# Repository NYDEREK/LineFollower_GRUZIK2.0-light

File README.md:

<h1 align="center">GRUZIK2.0: Line Follower Robot</h1>

<div align="center">

<i>Loved the project? Please consider giving a Star ⭐️</i>

</div>

> **GRUZIK2.0 is a lightweight construction (62g) designed for the "Line Follower Light" competition. The robot features Bluetooth communication with a smartphone app and uses a digital sensor instead of analog.**

<div align="center">
  
</div>

<div align="center">

</div>

## Hardware

> **The simple lightweight construction (74g) allows the robot to achieve high speed on the track.**
> **PCBs were designed in KiCAD 7.0 and manufactured by JLCPCB. The rims were 3D printed with PETG for Kyosho "Mini Z" tires.**
> **The light dualsky 150mAh battery provides enough current (max 30C) without adding too much weight (10g).**
> **The Pololu 2211 motor (10:1) with max current 1.6A per one requires the use of two separate TB6612FNG motor drivers with connected channels (max 2A per driver).**
> **The HC-05 Bluetooth module gives communication range up to 10m.**
> **The fast ARM microcontroller STM32F103C8T6 (max 72MHz) provides a lot of software capabilities.**

- uC - STM32F103C8T6
- drivers - TB6612FNG
- sensor - 8x KTIR0711S
- battery - 150mAh LiPo dualsky
- wheels - Kyosho Mini Z
- motors - Pololu 2211
- Bluetooth - HC-05

<div align="center">

</div>

## 📱Bluetooth Apps 📱

> **Thease are simple Bluetooth apps created with MIT App Inventor. Spps start and stop the robot. The Modes pad is responsible for quickly adapting the speed and accuracy of the robot to the route using modes, and the application also displays the battery charge status. Second app is mainly for tweaking PID settings it allows you to change any parameter in seconds**

<div align="center">

</div>

## Credits

> <i>**I implemented the PD controller in my project, drawing inspiration from Bilal Kabas' repository available at - https://github.com/sametoguten/STM32-Line-Follower-with-PID with MIT License - [MIT License](LICENSE)**<i>

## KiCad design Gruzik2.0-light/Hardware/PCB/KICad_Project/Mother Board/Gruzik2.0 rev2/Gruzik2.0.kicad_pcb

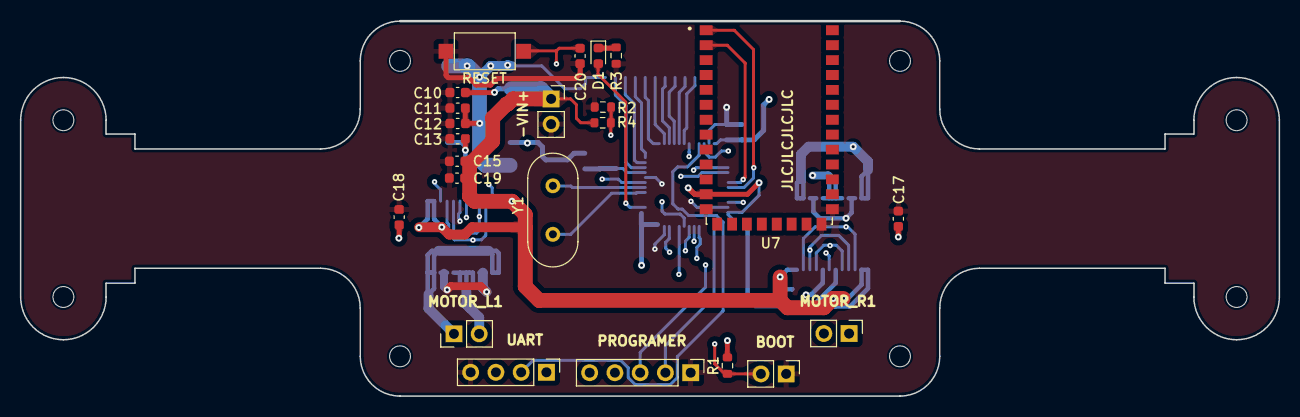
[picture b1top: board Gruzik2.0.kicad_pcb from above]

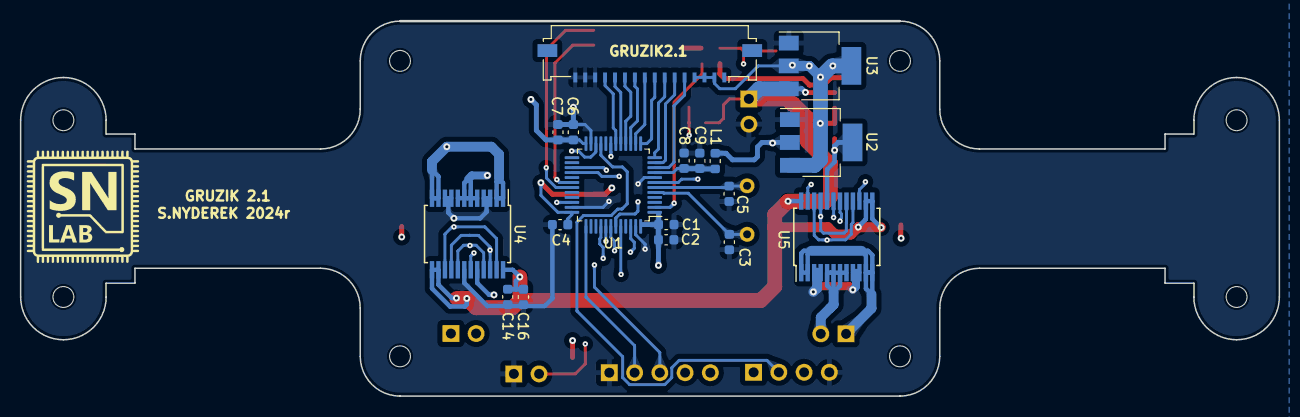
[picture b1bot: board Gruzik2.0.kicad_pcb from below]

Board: 4 copper layers, 126.5 x 37.7 mm, 41 parts (18 on the bottom side), 38 nets.

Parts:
-VIN+: Conn_01x02; PinSocket_1x02_P2.54mm_Vertical
BOOT: Conn_01x02_Pin; PinHeader_1x02_P2.54mm_Vertical
C1: 4u7; C_0603_1608Metric
C2, C4, C6, C7, C9, C20: 100n; C_0603_1608Metric
C3, C5: 20p; C_0603_1608Metric
C8: 1u; C_0603_1608Metric
C10, C12, C16, C19: 10u; C_0603_1608Metric
C11, C13: 33u; C_0603_1608Metric
C14, C15, C17, C18: 0.1u; C_0603_1608Metric
D1: BLUE; LED_0603_1608Metric
GRUZIK2.1: Conn_01x16; Molex_200528-0160_1x16-1MP_P1.00mm_Horizontal
L1: 27n; L_0603_1608Metric
MOTOR_L1: Conn_01x02; PinHeader_1x02_P2.54mm_Vertical
MOTOR_R1: Conn_01x02; PinHeader_1x02_P2.54mm_Vertical
PROGRAMER: Conn_01x05; PinHeader_1x05_P2.54mm_Vertical
R1: 10k; R_0603_1608Metric
R2: 20K; R_0603_1608Metric
R3: 510R; R_0603_1608Metric
R4: 33K; R_0603_1608Metric
RESET: SW_SPST; SW_SPST_CK_RS282G05A3
U1: STM32F103C8T6; LQFP-48_7x7mm_P0.5mm
U2: LM1117MP-3.3; SOT-223-3_TabPin2
U3: LM1117MP-5.0; SOT-223-3_TabPin2
U4, U5: TB6612FNG; SSOP-24_5.3x8.2mm_P0.65mm
U7: HC-05; XCVR_HC-05
UART: Conn_01x04; PinHeader_1x04_P2.54mm_Vertical
Y1: 8MHz; Crystal_HC49-4H_Vertical

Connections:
+3.3V: C1.1, C2.1, C4.1, C6.1, C7.1, C13.1, C17.1, C18.1, L1.1, R1.2, U1.1 (VBAT), U1.24 (VDD), U1.36 (VDD), U1.48 (VDD), U2.2 (VO), U4.20 (VCC), U5.20 (VCC), U7.12 (3.3_VCC)
+3.3VA: C8.1, C9.1, L1.2, U1.9 (VDDA)
+5V: C11.1, C12.1, GRUZIK2.1.2, GRUZIK2.1.3, GRUZIK2.1.4, PROGRAMER.5, U2.3 (VI), U3.2 (VO), UART.1
/BOOT0: BOOT.2, R1.1, U1.44 (BOOT0)
/HSE_IN: C5.1, U1.6 (PD1), Y1.2
/HSE_OUT: C3.1, U1.5 (PD0), Y1.1
GND: -VIN+.2, BOOT.1, C1.2, C2.2, C3.2, C4.2, C5.2, C6.2, C7.2, C8.2, C9.2, C10.2, C11.2, C12.2, C13.2, C14.2, C15.2, C16.2, C17.2, C18.2, C19.2, C20.1, GRUZIK2.1.14, GRUZIK2.1.15, GRUZIK2.1.16, PROGRAMER.1, R2.2, R3.2, RESET.1 (A), U1.8 (VSSA), U1.23 (VSS), U1.35 (VSS), U1.47 (VSS), U2.1 (GND), U3.1 (GND), U4.3 (PGND1), U4.4 (PGND1), U4.9 (PGND2), U4.10 (PGND2), U4.18 (GND), U5.3 (PGND1), U5.4 (PGND1), U5.9 (PGND2), U5.10 (PGND2), U5.18 (GND), U7.13 (GND), U7.21 (GND), U7.22 (GND), UART.4
unnamed: D1.1 (K), R3.1
unnamed: MOTOR_L1.1, U5.1 (AO1), U5.2 (AO1), U5.11 (BO1), U5.12 (BO1)
unnamed: MOTOR_L1.2, U5.5 (AO2), U5.6 (AO2), U5.7 (BO2), U5.8 (BO2)
unnamed: MOTOR_R1.1, U4.1 (AO1), U4.2 (AO1), U4.11 (BO1), U4.12 (BO1)
unnamed: MOTOR_R1.2, U4.5 (AO2), U4.6 (AO2), U4.7 (BO2), U4.8 (BO2)
PA0: GRUZIK2.1.5, U1.10 (PA0)
PA1: GRUZIK2.1.6, U1.11 (PA1)
PA2: GRUZIK2.1.7, U1.12 (PA2)
PA3: GRUZIK2.1.8, U1.13 (PA3)
PA4: GRUZIK2.1.9, U1.14 (PA4)
PA5: GRUZIK2.1.10, U1.15 (PA5)
PA6: GRUZIK2.1.11, U1.16 (PA6)
PA7: GRUZIK2.1.12, U1.17 (PA7)
PA9: U1.30 (PA9), U7.2 (UART-RX)
PA10: U1.31 (PA10), U7.1 (UART-TX)
PB0: GRUZIK2.1.13, U1.18 (PB0)
PB1: R2.1, R4.1, U1.19 (PB1)
PB4: U1.40 (PB4), U4.16 (BIN2), U4.22 (AIN2)
PB5: U1.41 (PB5), U4.17 (BIN1), U4.21 (AIN1)
PB6: U1.42 (PB6), U4.19 (STBY), U5.19 (STBY)
PB7: U1.43 (PB7), U5.15 (PWMB), U5.23 (PWMA)
PB9: U1.46 (PB9), U4.15 (PWMB), U4.23 (PWMA)
PB10: U1.21 (PB10), UART.2
PB11: U1.22 (PB11), UART.3
PB14: U1.27 (PB14), U5.17 (BIN1), U5.21 (AIN1)
PB15: U1.28 (PB15), U5.16 (BIN2), U5.22 (AIN2)
PC13: D1.2 (A), U1.2 (PC13)
RESET: C20.2, PROGRAMER.4, RESET.2 (B), U1.7 (NRST)
SWCLK: PROGRAMER.2, U1.37 (PA14)
SWDIO: PROGRAMER.3, U1.34 (PA13)
VDC: -VIN+.1, C10.1, C14.1, C15.1, C16.1, C19.1, R4.2, U3.3 (VI), U4.13 (VM2), U4.14 (VM3), U4.24 (VM1), U5.13 (VM2), U5.14 (VM3), U5.24 (VM1)

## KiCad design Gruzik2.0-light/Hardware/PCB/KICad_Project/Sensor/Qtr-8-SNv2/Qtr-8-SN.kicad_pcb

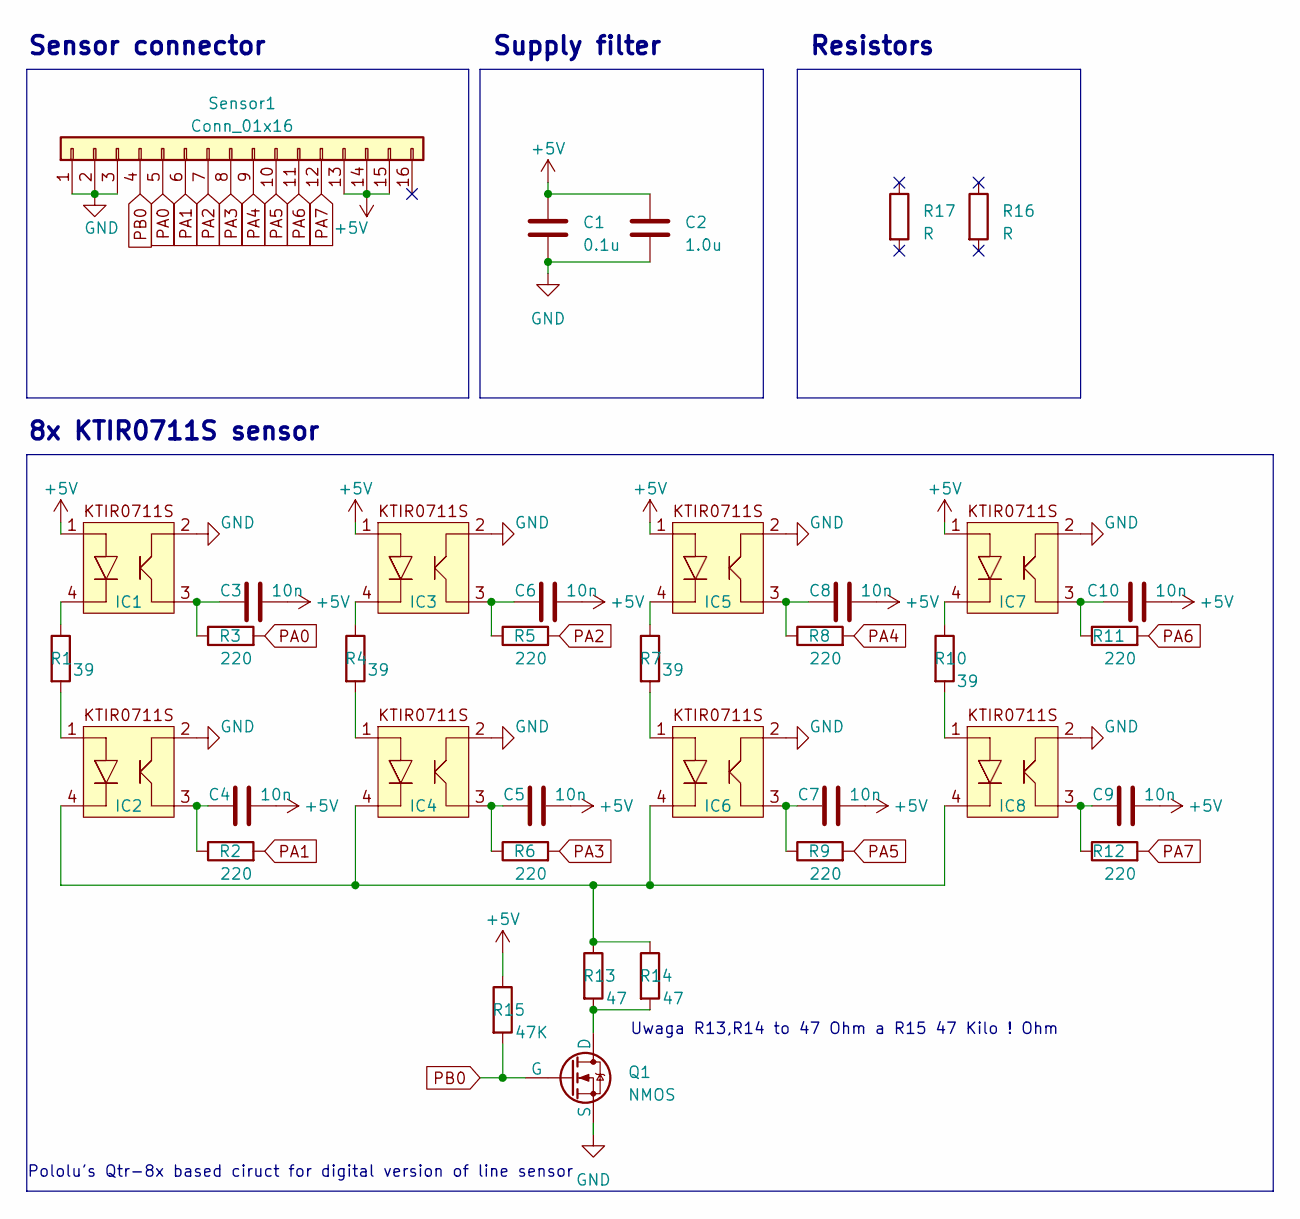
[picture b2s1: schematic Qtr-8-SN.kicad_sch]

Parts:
C1: 0.1u; C_0603_1608Metric
C2: 1.0u; C_0603_1608Metric
C3, C4, C5, C6, C7, C8, C9, C10: 10n; C_0603_1608Metric
IC1, IC2, IC3, IC4, IC5, IC6, IC7, IC8: KTIR0711S
Q1: NMOS; NMOS_SN
R1, R4, R7, R10: 39; R_0603_1608Metric
R2, R3, R5, R6, R8, R9, R11, R12: 220; R_0603_1608Metric
R13, R14: 47; R_0603_1608Metric
R15: 47K; R_0603_1608Metric
R16, R17: R; R_Axial_DIN0207_L6.3mm_D2.5mm_P7.62mm_Horizontal
Sensor1: Conn_01x16; Molex_200528-0160_1x16-1MP_P1.00mm_Horizontal

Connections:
+5V: C1.1, C2.1, C3.2, C4.2, C5.2, C6.2, C7.2, C8.2, C9.2, C10.2, IC1.1, IC3.1, IC5.1, IC7.1, R15.1, Sensor1.13, Sensor1.14, Sensor1.15; also elsewhere on the board
GND: C1.2, C2.2, IC1.2, IC2.2, IC3.2, IC4.2, IC5.2, IC6.2, IC7.2, IC8.2, Q1.3 (S), Sensor1.1, Sensor1.2, Sensor1.3; also elsewhere on the board
unnamed: C3.1, IC1.3, R3.1
unnamed: C4.1, IC2.3, R2.1
unnamed: C5.1, IC4.3, R6.1
unnamed: C6.1, IC3.3, R5.1
unnamed: C7.1, IC6.3, R9.1
unnamed: C8.1, IC5.3, R8.1
unnamed: C9.1, IC8.3, R12.1
unnamed: C10.1, IC7.3, R11.1
unnamed: IC1.4, R1.1
unnamed: IC2.1, R1.2
unnamed: IC2.4, IC4.4, IC6.4, IC8.4, R13.1, R14.1
unnamed: IC3.4, R4.1
unnamed: IC4.1, R4.2
unnamed: IC5.4, R7.1
unnamed: IC6.1, R7.2
unnamed: IC7.4, R10.1
unnamed: IC8.1, R10.2
unnamed: Q1.1 (D), R13.2, R14.2
PA0: R3.2, Sensor1.5; also elsewhere on the board
PA1: R2.2, Sensor1.6; also elsewhere on the board
PA2: R5.2, Sensor1.7; also elsewhere on the board
PA3: R6.2, Sensor1.8; also elsewhere on the board
PA4: R8.2, Sensor1.9; also elsewhere on the board
PA5: R9.2, Sensor1.10; also elsewhere on the board
PA6: R11.2, Sensor1.11; also elsewhere on the board
PA7: R12.2, Sensor1.12; also elsewhere on the board
PB0: Q1.2 (G), R15.2, Sensor1.4; also elsewhere on the board

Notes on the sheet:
Uwaga R13,R14 to 47 Ohm a R15 47 Kilo ! Ohm
Sensor connector
8x KTIR0711S sensor
Supply filter
Resistors
Pololu's Qtr-8x based ciruct for digital version of line sensor

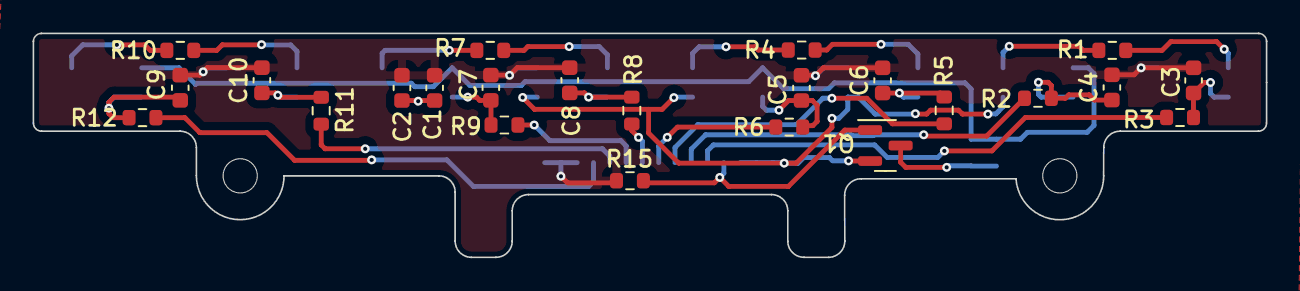
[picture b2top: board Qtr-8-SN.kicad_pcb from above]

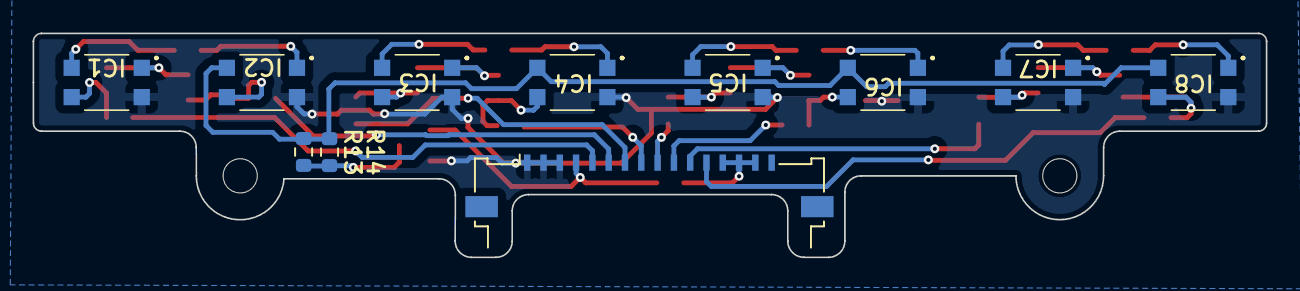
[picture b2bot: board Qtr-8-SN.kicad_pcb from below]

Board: 2 copper layers, 75.7 x 13.7 mm, 35 parts (11 on the bottom side), 29 nets.

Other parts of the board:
Sensor: Conn_01x16; Molex_200528-0160_1x16-1MP_P1.00mm_Horizontal

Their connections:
+5V: Sensor.13, Sensor.14, Sensor.15; also elsewhere on the board
GND: Sensor.1, Sensor.2, Sensor.3; also elsewhere on the board
PA0: Sensor.5; also elsewhere on the board
PA1: Sensor.6; also elsewhere on the board
PA2: Sensor.7; also elsewhere on the board
PA3: Sensor.8; also elsewhere on the board
PA4: Sensor.9; also elsewhere on the board
PA5: Sensor.10; also elsewhere on the board
PA6: Sensor.11; also elsewhere on the board
PA7: Sensor.12; also elsewhere on the board
PB0: Sensor.4; also elsewhere on the board

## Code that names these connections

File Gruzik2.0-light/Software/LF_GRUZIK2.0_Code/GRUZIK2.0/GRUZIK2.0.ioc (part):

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Mcu.Name=STM32F103C(8-B)Tx
Mcu.Package=LQFP48
Mcu.UserName=STM32F103C8Tx
PA0-WKUP.GPIOParameters=GPIO_Speed,GPIO_Label
PA0-WKUP.GPIO_Label=SENSOR8
PA0-WKUP.GPIO_Speed=GPIO_SPEED_FREQ_HIGH
PA0-WKUP.Signal=GPIO_Output
PA1.GPIOParameters=GPIO_Speed,GPIO_Label
PA1.GPIO_Label=SENSOR7
PA1.GPIO_Speed=GPIO_SPEED_FREQ_HIGH
PA1.Signal=GPIO_Output
PA10.Mode=Asynchronous
PA10.Signal=USART1_RX
PA13.Mode=Serial_Wire
PA13.Signal=SYS_JTMS-SWDIO
PA14.Mode=Serial_Wire
PA14.Signal=SYS_JTCK-SWCLK
PA2.GPIOParameters=GPIO_Speed,GPIO_Label
PA2.GPIO_Label=SENSOR6
PA2.GPIO_Speed=GPIO_SPEED_FREQ_HIGH
PA2.Signal=GPIO_Output
PA3.GPIOParameters=GPIO_Speed,GPIO_Label
PA3.GPIO_Label=SENSOR5
PA3.GPIO_Speed=GPIO_SPEED_FREQ_HIGH
PA3.Signal=GPIO_Output
PA4.GPIOParameters=GPIO_Speed,GPIO_Label
PA4.GPIO_Label=SENSOR4
PA4.GPIO_Speed=GPIO_SPEED_FREQ_HIGH
PA4.Signal=GPIO_Output
PA5.GPIOParameters=GPIO_Speed,GPIO_Label
PA5.GPIO_Label=SENSOR3
PA5.GPIO_Speed=GPIO_SPEED_FREQ_HIGH
PA5.Signal=GPIO_Output
PA6.GPIOParameters=GPIO_Label
PA6.GPIO_Label=SENSOR2
PA6.Signal=GPIO_Output
PA7.GPIOParameters=GPIO_Speed,GPIO_Label
PA7.GPIO_Label=SENSOR1
PA7.GPIO_Speed=GPIO_SPEED_FREQ_HIGH
PA7.Signal=GPIO_Output
PA9.Mode=Asynchronous
PA9.Signal=USART1_TX
PB0.GPIOParameters=GPIO_Speed,GPIO_Label
PB0.GPIO_Label=LEDON
PB0.GPIO_Speed=GPIO_SPEED_FREQ_HIGH
PB0.Signal=GPIO_Output
PB1.Signal=ADCx_IN9
PB10.Mode=Asynchronous
PB10.Signal=USART3_TX
PB11.Mode=Asynchronous
PB11.Signal=USART3_RX
PB14.GPIOParameters=GPIO_Speed,GPIO_Label
PB14.GPIO_Label=BIN1L
PB14.GPIO_Speed=GPIO_SPEED_FREQ_HIGH
PB14.Signal=GPIO_Output
PB15.GPIOParameters=GPIO_Speed,GPIO_Label
PB15.GPIO_Label=BIN1R
PB15.GPIO_Speed=GPIO_SPEED_FREQ_HIGH
PB15.Signal=GPIO_Output
PB4.GPIOParameters=GPIO_Speed,PinState,GPIO_Label
PB4.GPIO_Label=AIN2L
PB4.GPIO_Speed=GPIO_SPEED_FREQ_HIGH
PB4.PinState=GPIO_PIN_RESET
PB4.Signal=GPIO_Output
PB5.GPIOParameters=GPIO_Speed,GPIO_Label
PB5.GPIO_Label=AIN1R
PB5.GPIO_Speed=GPIO_SPEED_FREQ_HIGH
PB5.Signal=GPIO_Output
PB6.GPIOParameters=GPIO_Speed
PB6.GPIO_Speed=GPIO_SPEED_FREQ_MEDIUM
PB6.Signal=GPIO_Output
PB7.Signal=S_TIM4_CH2
PB8.Signal=S_TIM4_CH3
PB9.Signal=S_TIM4_CH4
PC13-TAMPER-RTC.GPIOParameters=PinState,GPIO_Label
PC13-TAMPER-RTC.GPIO_Label=LD
PC13-TAMPER-RTC.PinState=GPIO_PIN_SET
PC13-TAMPER-RTC.Signal=GPIO_Output
PD0-OSC_IN.Mode=HSE-External-Oscillator
PD0-OSC_IN.Signal=RCC_OSC_IN
PD1-OSC_OUT.Mode=HSE-External-Oscillator
PD1-OSC_OUT.Signal=RCC_OSC_OUT
RCC.SYSCLKFreq_VALUE=72000000
RCC.SYSCLKSource=RCC_SYSCLKSOURCE_PLLCLK
board=custom

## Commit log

2023-12-21 1.0
    Hardware done
2023-12-22 1.1
    Added ADC and constant motor speed
2023-12-24 1.2
    Speed modes done
2023-12-29 1.6
    Time mode - work in progress
2023-12-29 1.8 Time mode done
2023-12-29 Updated LICENSE
2024-01-02 1.9.1
2024-03-28 New Sensor
2024-03-28 1.9.2
    new sensor added
2024-04-12 2.0.1
    New sensor frame and upgraded software
2024-04-16 2.1.0
2024-04-21 2.1.3
    Added :
    - new app verssion
    - two new modes created on last competition
    deleted sharp bend couting
2024-04-21 2.1.4
    changed sensor mount
2024-07-09 2.1.5
    Mother board rev2
2024-07-12 2.1.6
    motherboard rev 2 update
2024-07-12 2.1.7
2024-10-17 2.1.8
    Added new rims & better main board :+1:
2024-10-20 2.2.1
    Added LF_studio, GRUZIK2.0 app rev2 and new communication protocol
2024-10-21 2.2.3
    New values for modes
2024-10-22 2.2.4
2024-11-13 2.3.1
    Added new features like new motor mounts new modes etc
